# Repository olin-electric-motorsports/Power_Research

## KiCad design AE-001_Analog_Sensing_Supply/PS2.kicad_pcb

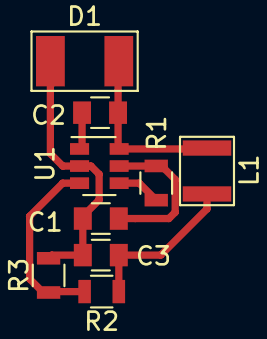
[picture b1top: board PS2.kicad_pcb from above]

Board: 2 copper layers, 9 parts (0 on the bottom side), 7 nets.

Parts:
C1: C_4.7uF_25V; C_0805_OEM
C2: C_10nF; C_0805_OEM
C3: C_10uF; C_0805_OEM
D1: CDBA140-G; DO-214AC
L1: L_2.2uH; BRL3225
R1: R_7.5M; R_0805_OEM
R2: R_49.9K; R_0805_OEM
R3: R_9.53K; R_0805_OEM
U1: AOZ1280; SOT-23-6_OEM

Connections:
/VIN: C1.2, R1.1, U1.5
/VOUT: C3.1, L1.2, R2.1
GND: C1.1, C3.2, D1.2, R3.2, U1.2
unnamed: C2.1, U1.1
unnamed: C2.2, D1.1, L1.1, U1.6
unnamed: R1.2, U1.4
unnamed: R2.2, R3.1, U1.3

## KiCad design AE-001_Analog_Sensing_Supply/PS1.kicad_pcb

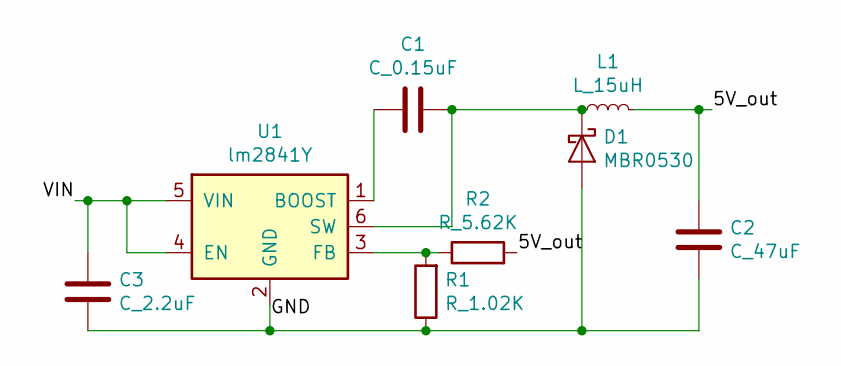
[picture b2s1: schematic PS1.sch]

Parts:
C1: C_0.15uF; C_0805_OEM; MPN 478-3352-1-ND
C2: C_47uF; C_0805_OEM; MPN 1276-6467-1-ND
C3: C_2.2uF; C_0805_OEM
D1: MBR0530; D_SOD-123
L1: L_15uH; L_100uH_OEM; MPN 445-1539-1-ND
R1: R_1.02K; R_0805_OEM; MPN P1.0KDACT-ND
R2: R_5.62K; R_0805_OEM; MPN P1.0KDACT-ND
U1: lm2841Y; LM2841Y

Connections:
/5V_out: C2.1, L1.2, R2.2
/GND: C2.2, C3.2, D1.2 (A), R1.1, U1.2 (GND)
/VIN: C3.1, U1.4 (EN), U1.5 (VIN)
unnamed: C1.1, D1.1 (K), L1.1, U1.6 (SW)
unnamed: C1.2, U1.1 (BOOST)
unnamed: R1.2, R2.1, U1.3 (FB)

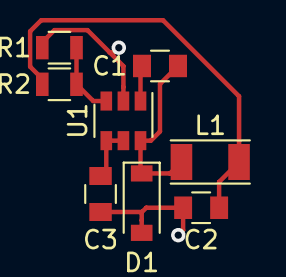
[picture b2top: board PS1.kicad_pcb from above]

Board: 4 copper layers, 8 parts (0 on the bottom side), 6 nets.

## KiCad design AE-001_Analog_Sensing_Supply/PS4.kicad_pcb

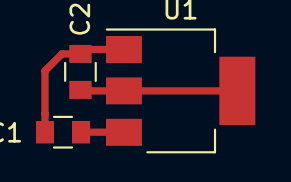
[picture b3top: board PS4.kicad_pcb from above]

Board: 2 copper layers, 3 parts (0 on the bottom side), 3 nets.

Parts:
C1: C_10uF_25V; C_0805_OEM
C2: C_10uF; C_0805_OEM
U1: NCP1117ST50T3G; SOT-223

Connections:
/Vin: C1.2, U1.3
/Vout: C2.1, U1.2, U1.4
GND: C1.1, C2.2, U1.1

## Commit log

2020-06-27 adding project file
2020-07-24 test schematic sheets
2020-07-24 lucky test edit test.sch
2020-07-24 fuk yeah this worked
2020-08-07 hopefully this shit works
2020-08-13 le buck
2020-08-14 PS2-Asynchronous Buck
2020-08-14 PS2-Async Buck
2020-08-21 le fresh buck
2020-08-21 Updated PS2
2020-08-27 updated buck
2020-08-28 updated buck ground labels
2020-08-28 ps2 changes
2020-08-28 fixed
2020-09-11 PS2 and PS4 layout
2020-09-11 updated layout for lm2841Y switching regulator, needs review
2020-09-18 buck layout v1
2021-02-13 updated schematic with correct parts and links
2021-02-13 testing collaborative layout
2021-02-13 sree's collaboration test
2021-02-13 circle
2021-02-13 4 test circles
